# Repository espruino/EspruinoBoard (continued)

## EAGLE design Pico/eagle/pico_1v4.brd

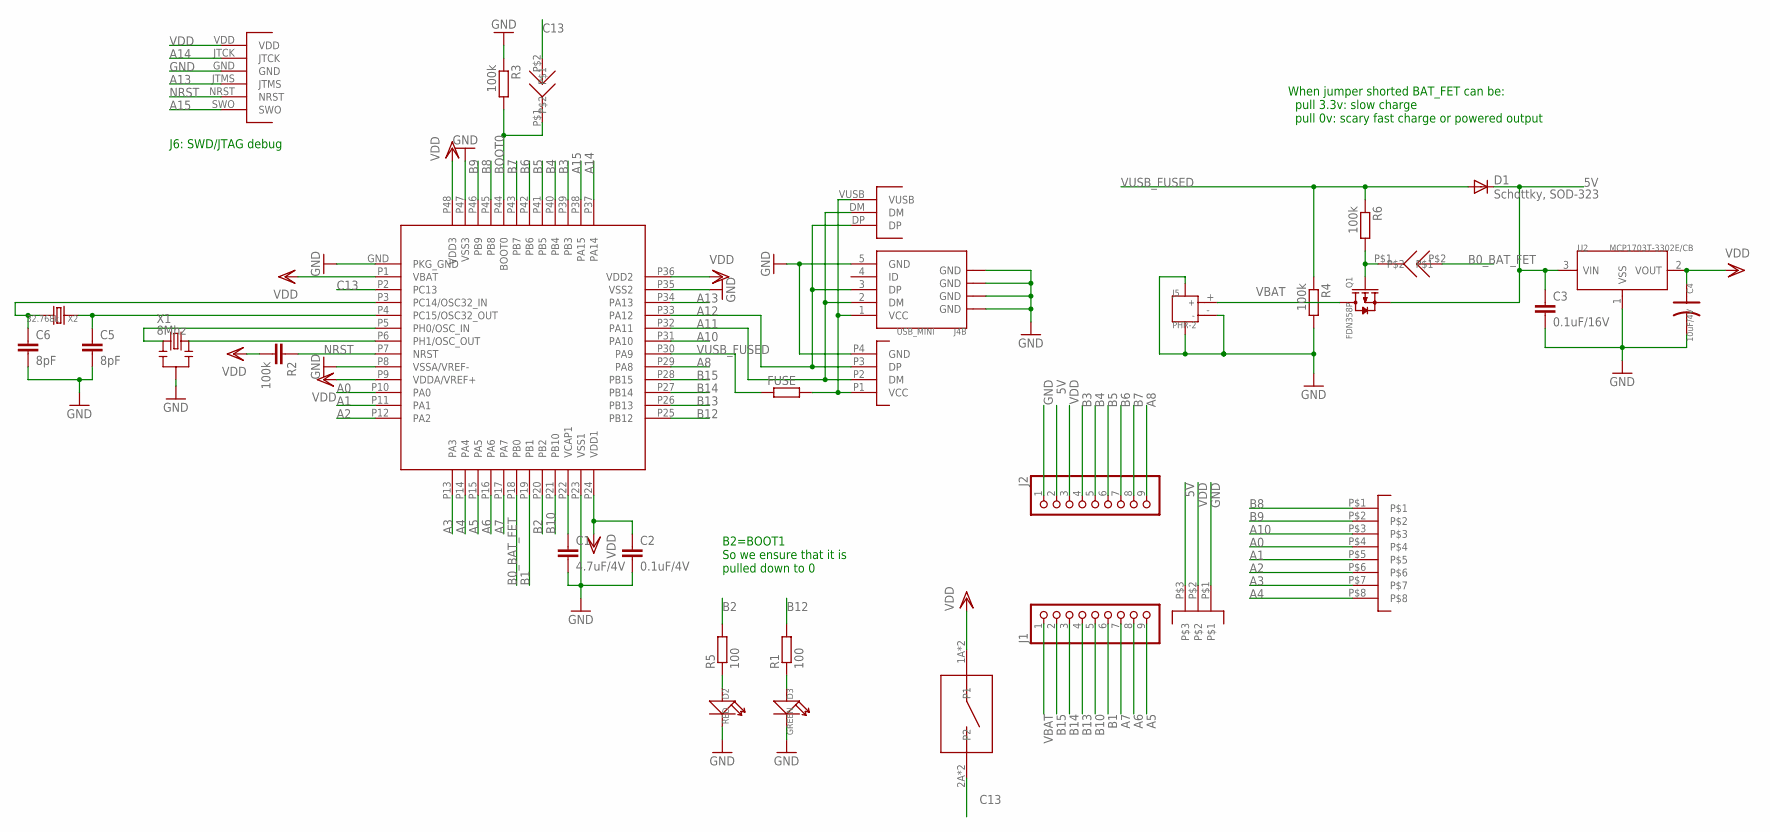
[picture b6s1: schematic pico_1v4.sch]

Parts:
B1: KMR421NG
C1: 4.7uF/4V; C0402
C2: 0.1uF/4V; C0402
C3: 0.1uF/16V; C0402
C4: 10uF/4V; AVX-A
C5, C6: 8pF; C0402
D1: Schottky, SOD-323; SOD323-W
D2: RED; LED-0402
D3: GREEN; LED-0402
FUSE: R-EU_R0603; R0603
J1, J2: PINHEAD9
J3, J7: SOLDERJUMPER
J4A: USB_TYPE_A_ONBOARD; USB_TYPEA_ONBOARD
J4B: USB_MINI
J5: PHR-2; JST-SMD-2.0-90D
J6: CON-SWD
J8: PINHEAD-1.27-8X1
J9: PINHEAD-1.27-3X1
Q1: FDN358P; SOT23
R1, R5: 100; R0402
R2: 100k; C0402
R3, R4, R6: 100k; R0402
U1: STM32F401CDU6; UFQFPN48
U2: MCP1703T-3302E/CB; SOT23
U$1: USB
X1: 8Mhz; 3P-SMD-3.6X1.3
X2: 32.768k; 2P-SMD-2.05X1.2

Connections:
5V: C3.1, D1.C, J2.2, J9.P$3, Q1.2 (S), U2.3 (VIN)
A0: J8.P$4, U1.P10 (PA0)
A1: J8.P$5, U1.P11 (PA1)
A2: J8.P$6, U1.P12 (PA2)
A3: J8.P$7, U1.P13 (PA3)
A4: J8.P$8, U1.P14 (PA4)
A5: J1.9, U1.P15 (PA5)
A6: J1.8, U1.P16 (PA6)
A7: J1.7, U1.P17 (PA7)
A8: J2.9, U1.P29 (PA8)
A10: J8.P$3, U1.P31 (PA10)
A11: J4A.P2 (DM), J4B.2 (DM), U1.P32 (PA11), U$1.DM
A12: J4A.P3 (DP), J4B.3 (DP), U1.P33 (PA12), U$1.DP
A13: J6.JTMS, U1.P34 (PA13)
A14: J6.JTCK, U1.P37 (PA14)
A15: J6.SWO, U1.P38 (PA15)
B0_BAT_FET: J3.P$2, U1.P18 (PB0)
B1: J1.6, U1.P19 (PB1)
B2: R5.2, U1.P20 (PB2)
B3: J2.4, U1.P39 (PB3)
B4: J2.5, U1.P40 (PB4)
B5: J2.6, U1.P41 (PB5)
B6: J2.7, U1.P42 (PB6)
B7: J2.8, U1.P43 (PB7)
B8: J8.P$1, U1.P45 (PB8)
B9: J8.P$2, U1.P46 (PB9)
B10: J1.5, U1.P21 (PB10)
B12: R1.2, U1.P25 (PB12)
B13: J1.4, U1.P26 (PB13)
B14: J1.3, U1.P27 (PB14)
B15: J1.2, U1.P28 (PB15)
BOOT0: J7.P$1, R3.2, U1.P44 (BOOT0)
C13: B1.2A (P2), B1.2B (P2), J7.P$2, U1.P2 (PC13)
GND: C1.3 (2), C2.3 (2), C3.3 (2), C4.- (2), C5.3 (2), C6.3 (2), D2.-, D3.-, J2.1, J4A.P4 (GND), J4B.5 (GND), J4B.P$1 (GND), J4B.P$2 (GND), J4B.P$3 (GND), J4B.P$4 (GND), J5.3, J5.4, J5.- (2), J6.GND, J9.P$1, R3.1, R4.2, U1.GND (PKG_GND), U1.P8 (VSSA/VREF-), U1.P23 (VSS1), U1.P35 (VSS2), U1.P47 (VSS3), U2.1 (VSS), X1.2
unnamed: C5.1, U1.P4 (PC15/OSC32_OUT), X2.1
unnamed: C6.1, U1.P3 (PC14/OSC32_IN), X2.2
unnamed: U1.P5 (PH0/OSC_IN), X1.1
unnamed: U1.P6 (PH1/OSC_OUT), X1.3
unnamed: D2.+, R5.1
unnamed: D3.+, R1.1
unnamed: J3.P$1, Q1.1 (G), R6.2
unnamed: C1.1, U1.P22 (VCAP1)
NRST: J6.NRST, R2.1, U1.P7 (NRST)
VBAT: J1.1, J5.+ (1), Q1.3 (D)
VDD: B1.1A (P1), B1.1B (P1), C2.1, C4.+ (1), J2.3, J6.VDD, J9.P$2, R2.3 (2), U1.P1 (VBAT), U1.P9 (VDDA/VREF+), U1.P24 (VDD1), U1.P36 (VDD2), U1.P48 (VDD3), U2.2 (VOUT)
VUSB: FUSE.2, J4A.P1 (VCC), J4B.1 (VCC), U$1.VUSB
VUSB_FUSED: D1.A, FUSE.1, R4.1, R6.1, U1.P30 (PA9)

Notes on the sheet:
When jumper shorted BAT_FET can be: pull 3.3v: slow charge pull 0v: scary fast charge or powered output
B2=BOOT1 So we ensure that it is pulled down to 0
J6: SWD/JTAG debug

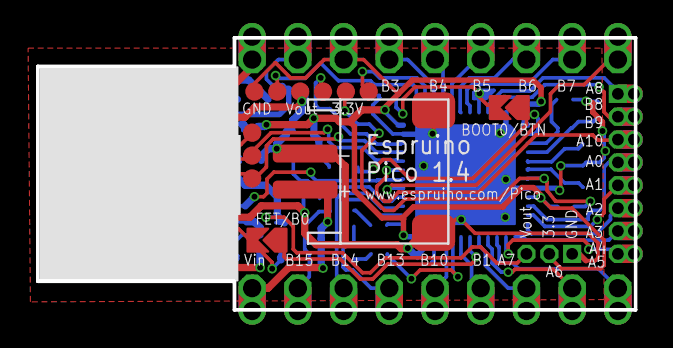
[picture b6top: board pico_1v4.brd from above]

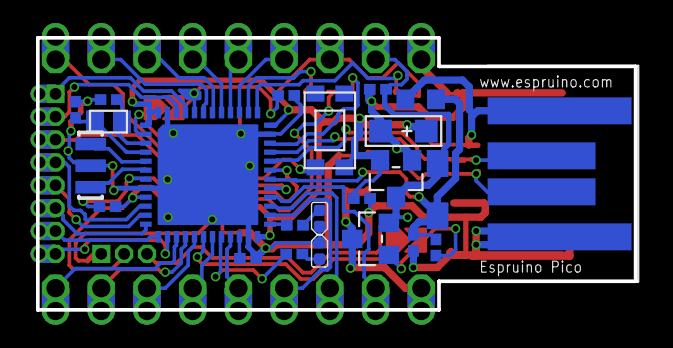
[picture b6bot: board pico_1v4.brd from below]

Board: 2 copper layers, 33.2 x 15.1 mm, 33 parts (23 on the bottom side), 47 nets.

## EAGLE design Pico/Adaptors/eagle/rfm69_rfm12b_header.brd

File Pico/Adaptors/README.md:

Here we have a selection of adaptor 'shims' to connect the Espruino Pico to various other devices. 

There's [a forum thread](http://forum.espruino.com/conversations/259519/) on potential adaptors. So far we have:

Available
--------

Unless specifically marked these are currently untested - use at your own risk.

| Link | Type |
|------|------|
|  |  Arduino/classic Espruino footprint |
|  |  Gameboy-style buttons - **Tested** |
|  |  NRF24L01P wireless |
|  |  NRF24L01P wireless (using 0.05 inch pins) |
|  | ESP8266 ESP01 WiFi Shim rev 1 - **Tested** |
|  | ESP8266 ESP01 WiFi Shim rev 2 - **Tested** - [buy on Tindie!](https://www.tindie.com/products/gfwilliams/espruino-pico-esp8266-wifi-shim/) |
|  |  ESP8266 ESP12 (SMD) WiFi - using 0.05 inch on end of board  |
|  |  ESP8266 ESP12 (SMD) WiFi  - using only 0.1 inch pins |
|  |  WIZnet W5500 Ethernet - **Tested**  - [buy on Tindie!](https://www.tindie.com/products/gfwilliams/espruino-pico-wiznet-w550io-ethernet-shim/) |
|  |  Generic XBee footprint (will handle SRF via the XRF module) |
|  | RFM12B  wireless |
|  |  RFM69HW wireless |
|  |  RFM12B/RFM69HW wireless using only 0.1 inch pins |
|   |  HC-05 / HC-06 / HM-10 bluetooth |
|   |  HC-05 / HC-06 / HM-10 bluetooth using only 0.1 inch pins |
|  |  Model aircraft servos |
|  |  Micro SD card - flat shim (small, but hard to get at pins) |
|  |  Micro SD card using only 0.1 inch pins |
|   |  (DaveCJ) Screw terminals |
|  |  Line-following Robot (LEDs, Mouse sensor, 4x LDRs, 4x Servo, Bluetooth, WiFi) |
|  |  Simple Line-following Robot (LEDs, 4x LDRs, 2x Servo, Bluetooth) |
|  |  [Seeed Studio Grove System](http://www.seeedstudio.com/depot/s/grovefamily.html) |
|  |  0.05" to 0.1" adaptor |
|  |   0.05" to 0.1" adaptor and Prototyping area (thin) |
|  |   0.05" to 0.1" adaptor and Prototyping area (wide) |
| [Link](../EspruBoy/espruboy.brd) | Mini-GameBoy Module |

To get one made, copy the `.brd` file linked and upload it to a company like [OSH Park](https://www.oshpark.com/) or [DirtyPCBs](http://dirtypcbs.com/).

Possibly To Do
------------

| Link | Type |
|------|------|
|  |  Mounting Holes |
|  |  MAX1551 LiPo battery charger |
|  |  CC3000 WiFi |
|  |  Audio Jack (see the [Audio programming thread](http://forum.espruino.com/conversations/257732/)) |
|  |  Dual H-bridge motor driver (i'm open to ideas for something cheap and easily sourceable) |
|  |  20x4 LCD |
|  |  Wii Nunchuck |
|  |  (DrAzzy) AT24 I2C EEPROM, or AT25 SPI EEPROM - I think one or the other would be helpful? I've put EEPROMs onto the prototyping area on 2 of my 3 Espruinos - there are just so many times working with a microcontroller when you want to store just a few bytes in non-volatile memory. |
|  |  (DrAzzy) ULN2003/2803 board (put the pads for a 2803, if we want to use a 2003, it could be installed, just not using the last pair of pads), giving us 7/8 higher current outputs on 0.1" header |
|  |  (DrAzzy) SOT-23 MOSFET board - as with the ULN2003/2803, only with a buncha mosfets, with pads for a resistor between gnd and each gate for a pulldown |
|  |  (DaveCJ) [Sx1272/RFM92 868Mhz radio](http://www.ebay.co.uk/itm/HopeRF-RFM92W-915Mhz-LoRa-Ultra-Long-Range-Transceiver-SX1272-compatible-/181415801105) |
|  |  (thomc) SMT proto area (like [this](http://www.adafruit.com/product/1212)) |
|  |  (DrAzzy) A MAX31855 thermocouple interface, with spot for screw terminals to connect the thermocouple |
|  |  Soil moisture sensor |
|  |  Capacitive keypad |
|  |  [LPRS eRIC](http://www.lprs.co.uk/easy-radio/eric/) radio module |
|  |  [.NET Gadgeteer](http://www.netmf.com/gadgeteer/) |

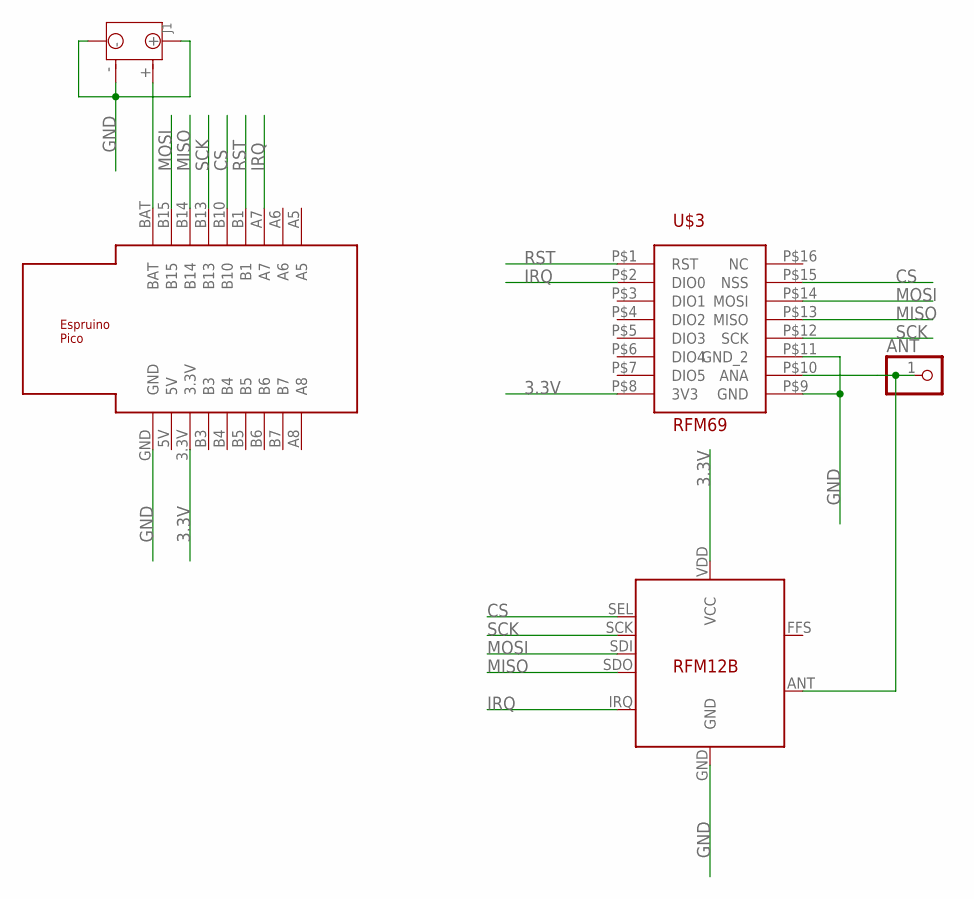
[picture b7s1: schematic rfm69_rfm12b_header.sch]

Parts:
ANT: PINHD-1X1; 1X01
J1: JST-2P-SMD-PW-3410050P1; 2P-SMD-2.0-90D
U$1: ESPRUINO_PICO_0.1
U$2: RFM12B
U$3: RFM69

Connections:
3.3V: U$1.3.3V, U$2.VDD (VCC), U$3.P$8 (3V3)
CS: U$1.B10, U$2.SEL, U$3.P$15 (NSS)
GND: J1.3, J1.4, J1.-, U$1.GND, U$2.GND, U$3.P$9 (GND), U$3.P$11 (GND_2)
IRQ: U$1.A7, U$2.IRQ, U$3.P$2 (DIO0)
MISO: U$1.B14, U$2.SDO, U$3.P$13 (MISO)
MOSI: U$1.B15, U$2.SDI, U$3.P$14 (MOSI)
unnamed: ANT.1, U$2.ANT, U$3.P$10 (ANA)
unnamed: J1.+, U$1.BAT
RST: U$1.B1, U$3.P$1 (RST)
SCK: U$1.B13, U$2.SCK, U$3.P$12 (SCK)

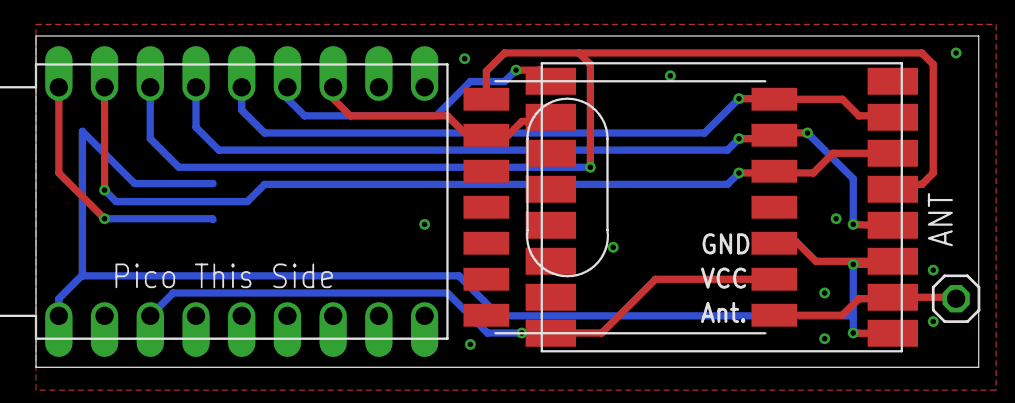
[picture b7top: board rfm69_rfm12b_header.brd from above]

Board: 2 copper layers, 52.4 x 18.4 mm, 5 parts (1 on the bottom side), 10 nets.

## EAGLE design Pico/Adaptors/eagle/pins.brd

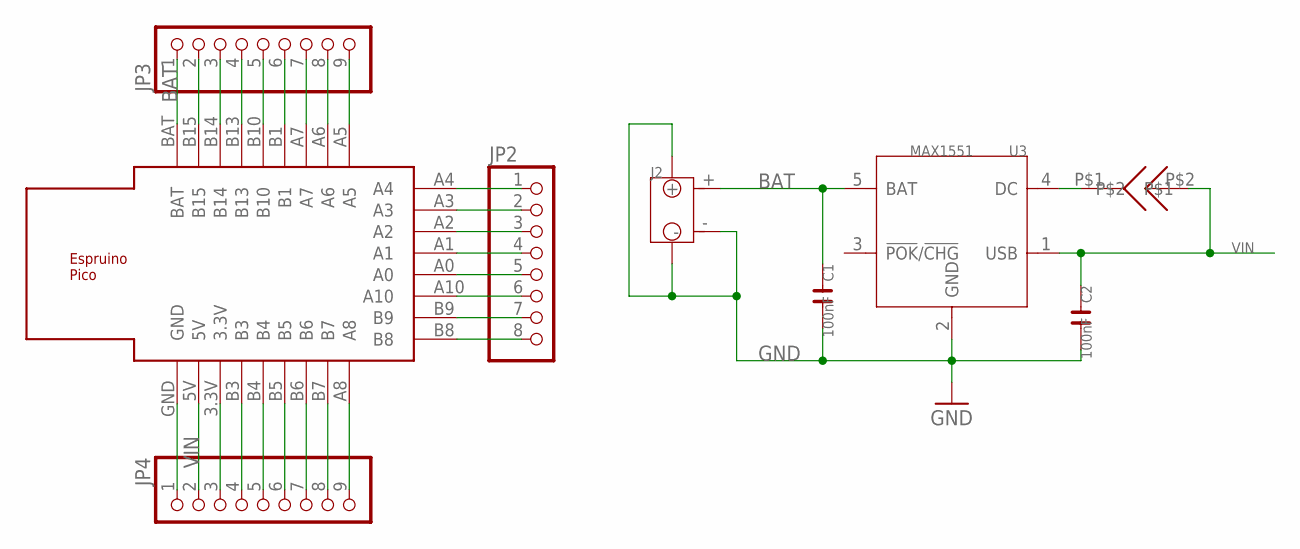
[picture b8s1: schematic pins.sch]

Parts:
C1, C2: 100nF; C0603
J2: JST-2P-SMD-PW-3410050P1; 2P-SMD-2.0-90D
JP2: PINHD-1X08_2.54-S; 1X08-S
JP3, JP4: PINHD-1X09_2.54-S; 1X09-S
U3: MAX1551; SOT23-5
U$1: ESPRUINO_PICO_SMD
U$4: SOLDERJUMPER

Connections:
BAT: C1.1, J2.+, JP3.1, U3.5 (BAT), U$1.BAT
GND: C1.2, C2.2, J2.3, J2.4, J2.-, JP4.1, U3.2 (GND), U$1.GND
unnamed: JP2.2, U$1.A3
unnamed: JP2.3, U$1.A2
unnamed: JP2.4, U$1.A1
unnamed: JP2.5, U$1.A0
unnamed: JP2.6, U$1.A10
unnamed: JP2.7, U$1.B9
unnamed: JP4.3, U$1.3.3V
unnamed: JP4.4, U$1.B3
unnamed: JP2.8, U$1.B8
unnamed: JP4.5, U$1.B4
unnamed: JP4.6, U$1.B5
unnamed: JP4.7, U$1.B6
unnamed: JP4.8, U$1.B7
unnamed: JP4.9, U$1.A8
unnamed: U3.4 (DC), U$4.P$1
unnamed: JP3.2, U$1.B15
unnamed: JP3.3, U$1.B14
unnamed: JP3.4, U$1.B13
unnamed: JP3.5, U$1.B10
unnamed: JP3.6, U$1.B1
unnamed: JP3.7, U$1.A7
unnamed: JP3.8, U$1.A6
unnamed: JP3.9, U$1.A5
unnamed: JP2.1, U$1.A4
VIN: C2.1, JP4.2, U3.1 (USB), U$1.5V, U$4.P$2

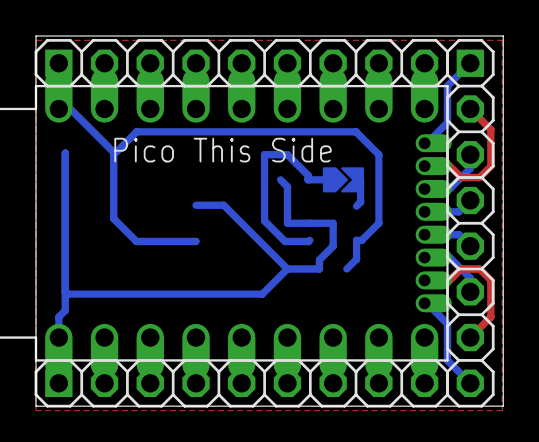
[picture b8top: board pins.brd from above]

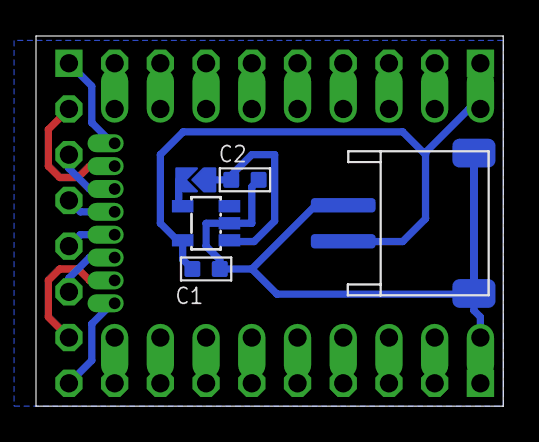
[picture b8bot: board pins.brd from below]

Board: 2 copper layers, 26.0 x 20.6 mm, 9 parts (5 on the bottom side), 27 nets.

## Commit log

2013-10-16 BTN->BOOT0 on silkscreen
2013-10-16 Move gnd via away from battery connector
2013-10-16 mid-tweak on 1v3, pins for LED re-assigned
2013-10-17 Espruino 1.3 complete first try
2013-10-18 fred's tweaks
2013-10-18 tweak some vias, improve silk screen
2013-10-18 final checks, added unpopulated pull-up resistor just in case
2013-10-18 more silk screen fun
2013-11-08 espruino 1v3b, with a few via tweaks and no silkscreen over vias. gerber files added
2013-11-13 new pdfs
2013-12-03 Espruino 3D printable boxes
2013-12-03 one more box
2014-02-04 added fritzing part
2014-02-05 Update Espruino.fzpz Add Espruino1v3.svg Add ScreenShort_1v3.jpg Add espruino_icon.svg Espruino.fzpz link all the middle pin
2014-02-05 tidying, remove duplicate files
2014-04-19 Makefile for OpenSCAD files
2015-02-10 finally added pico outline
2015-02-10 oops
2015-02-12 start of arduino, added classic espruino part
2015-02-16 added bluetooth adaptor
2015-02-20 nrf24 adaptor, and DRC
2015-02-20 arduino adaptor
2015-02-20 tweaking
2015-03-05 W550io
2015-03-05 oops - fix wiznet board
2015-03-05 docs
2015-03-09 xbee and rfm12b modules
2015-03-13 more tweaks and options
2015-03-16 update for dirtypcbs
2015-04-21 add case for 1.4 and test print
2015-04-21 fix stupid url mistake
2015-04-21 update README into <1.4 and 1.4 sections
2015-04-23 Box for the Espruino Pico.
2015-04-28 add cover
2015-04-28 fix formatting so that image breaks from paragraph
2015-05-05 Added Pico Fritzing library
2015-05-06 Quick and dirty rfm69 with DrAzzy's part
2015-05-06 updated NRF24, new Pico library part that does 0.1 holes and 0.05 SMD
2015-05-12 added robot shield, and tweaked RFM69 shim (getting protos made)
2015-05-21 add espruboy
2015-05-21 watch bettery holder
2015-05-22 added ESP12 shim
2015-05-27 add irq line
2015-06-09 make tab big enough for LCD
2015-06-09 fix shorted cr2032 battery connection
2015-06-24 connect Vin and 5V, allowing shields to be powered from USB volts
2015-06-26 todo
2015-06-26 added another ultrasonic sensor, pins down the side, and ADNS5050 optical sensor
2015-07-02 added pico 1v3 board
2015-07-02 rename
2015-07-13 add photo
2015-07-14 add resist over vias
2015-08-05 new, simpler robot board. Just sent to board house so fingers crossed :)
2015-08-12 small gameboy-style buttons for Espruino Pico
2015-08-13 added library part with 2 pins missing, and ESP8266 shim that should fit on pinned boards
2015-08-20 rotate ultrasonic, add fast charge
2015-09-18 Add I2C pullup
2015-09-18 misc tweaks
2015-09-18 added 0.1 inch only pico
2015-09-18 add ESP12 adaptor for 0.1 inch
2015-09-21 tweaked robot design - swap LEDs, add optional bluetooth
2015-09-21 tool for making thumbnails
2015-09-21 tweak net classes
2015-09-21 pics
2015-09-21 add button shield
2015-09-21 Add SeeedStudio Grove adaptor
2015-09-21 more boards
2015-09-21 grounding
2015-09-21 move board around
2015-09-22 first try at panellisation
2015-09-22 a full panel
2015-09-22 oops 2
2015-09-22 panel sent
2015-09-22 production tweaks
2015-10-07 minor board tweaks
2015-11-04 add version number and url
2015-11-16 fixes for SD card adaptor
2015-11-19 add JST connector to pins, update thumbnails
2015-11-19 added battery charger IC
2015-11-19 Added battery charger pads to proto headers
2015-11-23 updated fritzing Pico with 0.05 pins and layout
2016-01-06 pico 1v4
2016-08-15 kicad module for pico - courtesy of user66772
2017-01-11 Adding Puck and WiFi design files
2017-01-11 improve readme
2017-02-03 bottom.stl from bottom.stp, so aligned to axis
2017-03-27 adding espruino logo 3d model
2018-03-07 add mdbt42 lib
2018-05-15 pixl.js
2018-06-27 add breakout and beacon example
2018-09-25 Other Pixl.js files
2019-03-17 buy from espruino shop
2019-03-18 Update README.md
    Update links
2020-07-14 fix #11
2020-07-14 Puck v2 schematic
2020-10-28 Add Bangle.js dock
2021-03-26 add banglejs form
2021-11-01 stand
2021-11-02 shorter stand
2021-11-02 tweaks for usable 1 pc holder
2021-11-02 Working version with p1 plate
2022-02-24 remove un-needed file
2022-02-24 add 3d version
2022-02-24 Add STL of watch body
2022-05-10 new pcb rev
2023-09-11 new case designs, and a readme
2024-07-12 add jolt schematics
2025-03-12 add board
2025-03-12 updated PDF that maybe GitHub can render
